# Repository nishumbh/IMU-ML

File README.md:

# Knee rehabilitation: IMU-only offline model training

Research pipeline for knee rehabilitation form assessment using KneE-PAD IMU
data: verified release ingestion, preprocessing, subject-disjoint evaluation,
and saved scikit-learn models. **Current scope is offline training and model
storage, not embedded deployment.** This is not a clinical model or a
safety-certified device.

The local `data/raw/dataset` release has 2,086 trials from 31 participants. Its
48-channel layout, 148.14814814814815 Hz rate, units and nine source class IDs
were checked against the [release metadata](https://zenodo.org/records/12112951)
and [paper](https://doi.org/10.1038/s41597-025-04963-4). Separate squat, seated
leg-extension and gait manifests preserve the two documented errors per task.
Two gait files are empty and require explicit, recorded exclusion.

**Important limits:** the reference models use all eight IMUs (48 channels),
not a single-IMU knee brace. Use `--sensor-ids` to define a fixed subset and
retrain/evaluate it separately. No injured-side swapping, mirroring or frame
alignment is inferred. Generic manifest templates still need verified mappings
for other releases. Supplementary pretraining/domain adaptation is not
implemented. TensorFlow remains optional; embedded functionality is deferred.

## Two-strap ESP32-C3 prototype

For the **two-board MicroPython + ESP-NOW + master SD** implementation, see
[`tech/iot/README.md`](tech/iot/README.md). It has hardcoded bench and provisioned
OTA-capable iterations. Mechanical/electronics assets remain in `tech/designs/`.
The older Arduino sketch below is a separate, single-board acquisition example.

For the above-knee / below-knee two-IMU hardware, start with
[docs/TWO_STRAP_TEAM_GUIDE.md](docs/TWO_STRAP_TEAM_GUIDE.md). It covers wiring,
SD logging, sensor placement, CSV format and the local browser interface.

```bash
# Run from project root; review-only, no hardware/model required:
PYTHONPATH=src python -m knee_rehab.interface
# Enable offline research predictions using a separately trained 12-channel model:
PYTHONPATH=src python -m knee_rehab.interface \
  --model-dir artifacts/knee_pad_extension_two_imu_rf_v1
```

Open `http://127.0.0.1:8080` and upload the SD recording. The example Arduino
logger is `firmware/two_imu_logger/two_imu_logger.ino` (two **MPU6050** modules;
change drivers for other IMUs). This is SD-to-computer review, not live medical
feedback or on-ESP32 inference. Firmware hardware testing remains outstanding.
The two-sensor models were genuinely retrained on thigh/shank source sensors,
not padded to imitate eight sensors. Their performance is limited; see the
team guide before interpreting any prediction.

## Directory layout

```text
.
├── README.md
├── pyproject.toml
├── requirements.txt
├── configs/
│   ├── manifest.example.json               # Numeric KneE-PAD NPY mapping template
│   ├── manifest.csv.example.json           # Supplementary CSV mapping template
│   └── resource_measurements.example.json  # Null/unverified: intentionally fails gate
├── src/knee_rehab/
│   ├── __init__.py
│   ├── data_loader.py                      # Explicit, SI-unit IMU-only NPY/CSV ingestion
│   ├── preprocess.py                       # Resampling, causal DSP, windows, cheap features
│   ├── baseline.py                         # Bounded RF and scaled RBF SVM; LOSO
│   ├── models.py                           # Compact temporal CNN; fold-local channel scaling
│   ├── evaluate.py                         # Fixed confusion matrices + false acceptance
│   ├── export.py                           # Training-calibrated full-int8 TFLite export
│   ├── check_resources.py                  # Fail-closed measured-resource gate
│   └── train.py                            # CLI + artifacts/provenance
├── scripts/create_demo_data.py             # SYNTHETIC mixed-format smoke test only
├── tests/
│   ├── test_data_loader.py
│   ├── test_preprocess.py
│   ├── test_evaluation.py
│   ├── test_resources.py
│   └── test_export.py                      # Skipped without TensorFlow
├── docs/DATASETS.md                        # Mapping, alignment, labels, integration rules
├── firmware/README.md                      # MCU numerical parity and memory acceptance
├── data/
│   ├── raw/                               # External, untracked, immutable sources
│   ├── interim/                           # Verified conversions/alignment
│   └── processed/                         # Optional cached windows/features
├── artifacts/                             # One new/empty directory per training run
└── notebooks/                             # Optional exploratory analysis
```

## Install and run

Python 3.10–3.13; Python 3.11/3.12 is a practical choice for TensorFlow wheel
availability on supported platforms.

```bash
python -m venv .venv
source .venv/bin/activate
python -m pip install -r requirements.txt
python -m pip install -e .

# No dataset credentials required: SYNTHETIC pipeline smoke test only
python scripts/create_demo_data.py
python -m knee_rehab.train \
  --manifest data/demo_manifest.json --output-dir artifacts/demo_rf \
  --model rf --correct-threshold 0.9

python -m knee_rehab.train \
  --manifest data/demo_manifest.json --output-dir artifacts/demo_svm \
  --model svm --correct-threshold 0.9

# Tests work with the standard library, without pytest
PYTHONPATH=src python -m unittest discover -s tests -v
# Or: pip install -e '.[dev]' && pytest
```

Synthetic results test plumbing, **not** rehabilitation accuracy. The demo has
four fake participants and three deliberately separable simulated classes. Use
a distinct empty output directory for every run to prevent stale model/report
mixups. Recent scikit-learn versions may warn that SVC's probability API is
being deprecated; this baseline currently uses that API.

For real data, copy a manifest template, replace all placeholders from the
actual release and follow [docs/DATASETS.md](docs/DATASETS.md). Then:

```bash
python -m knee_rehab.train \
  --manifest configs/my_verified_knee_pad.json \
  --output-dir artifacts/knee_pad_rf_v1 --model rf \
  --target-rate-hz 50 --cutoff-hz 10 --filter-order 4 \
  --window-seconds 2 --overlap 0.5 --correct-threshold 0.9
```

`0.9` is an **illustrative prespecified threshold**, not a validated safety
setting. Estimate a clinically acceptable operating point using inner,
subject-disjoint validation and a separate outer/prospective evaluation. Do not
tune a threshold on the held-out participant.

## Train and store models from the local release

The completed reference run and saved artifact paths are documented in
[docs/TRAINING_RESULTS.md](docs/TRAINING_RESULTS.md), including the low recall
at the illustrative 0.9 threshold and the source exclusions.

Run from the project root. No TensorFlow, firmware, quantization, or target
hardware is required for the random forest models. Pick new manifest/output
paths if these already exist; the commands intentionally refuse overwrites.

```bash
# Build exercise-specific manifests; checks shapes, units and source SHA-256.
for exercise in extension squat gait; do
  python -m knee_rehab.knee_pad \
    --dataset-dir data/raw/dataset --exercise "$exercise" --skip-empty \
    --output "data/interim/knee_pad_${exercise}_all_imus.json"
done

# LOSO evaluation, followed by a final fit on all available subjects.
for exercise in extension squat gait; do
  python -m knee_rehab.train \
    --manifest "data/interim/knee_pad_${exercise}_all_imus.json" \
    --output-dir "artifacts/knee_pad_${exercise}_rf_v1" \
    --model rf --correct-threshold 0.9
done
```

`--skip-empty` only permits explicit exclusion of fewer-than-two-sample trials;
NaN/Inf, unknown class folders and invalid channel layouts still fail. Excluded
paths, shapes, reasons and hashes are retained in the manifest. The two empty
files are `Subject_18/6/Trial_1/imu.npy` and `Subject_27/6/Trial_1/imu.npy`.
Raw files are never modified. All eight fixed anatomical sensor placements are
used by default. For a single fixed right rectus femoris IMU, build a **new**
manifest with `--sensor-ids 1`; this is not automatically the injured leg.

Each output directory stores:

- `final.joblib`: final RF pipeline, fitted on all included subjects;
- `cv_results.json`: held-out-subject and pooled raw/conservative results;
- `metadata.json`: ordered channels, labels, preprocessing, window/subject
  counts, skipped recordings, source hashes and Python/package versions;
- `feature_config.json`, `feature_names.json`: exact feature mapping;
- `input_manifest.json`: original mapping/provenance snapshot. Its relative
  paths are anchored to the original `manifest_path` in metadata, not to the
  snapshot's new directory; use the original manifest for replay.

`artifacts/` and `data/interim/` are gitignored: keep a separate backup of model
artifacts and manifests. Joblib files must only be loaded from trusted sources,
using compatible package versions (recorded in metadata).

### Reload for offline predictions

```bash
python -m knee_rehab.predict \
  --model-dir artifacts/knee_pad_extension_rf_v1 \
  --manifest data/interim/knee_pad_extension_all_imus.json \
  --output artifacts/extension_predictions.json
```

This reuses saved preprocessing and checks channel compatibility. Predictions
on the training manifest are a persistence/plumbing check, **not** a new test
score; use `cv_results.json` for LOSO results. The exercise must already be known:
these are three form models, not an automatic exercise recognizer. Gait has far
fewer trials and missing class coverage per subject. A 0.9 rejection threshold
is illustrative, not clinically validated; low false acceptance alone does not
mean useful correct-form recall.

## Data loading and preprocessing APIs

```python
from knee_rehab.data_loader import load_manifest
from knee_rehab.preprocess import PreprocessConfig, prepare_windows, extract_features

recordings = load_manifest("configs/my_verified_knee_pad.json")
batch = prepare_windows(recordings, PreprocessConfig(
    target_rate_hz=50, cutoff_hz=10, filter_order=4,
    window_seconds=2, overlap=0.5,
))
features, names = extract_features(batch.X, batch.sample_rate_hz)
# batch.X: float32 [windows, 100 samples, channels]
# batch.y / batch.subject_ids / batch.recording_ids: one value per window
# Six IMU channels -> features.shape == (windows, 84)
```

Each manifest record is one contiguous, constant-label, single-subject trial
segment. Paths are relative to the manifest. Only selected acceleration and
rotation channels are read into model inputs; sEMG, pressure, magnetometer,
subject information and labels never become features. Subject information is
retained only for grouping/evaluation. Acceleration/rotation are converted to
m/s² and rad/s. Missing/invalid readings and irregular timestamps are rejected
rather than silently dropping rows or mixing samples across gaps.

Processing order per record:

1. `resample_poly`: rational polyphase conversion, including anti-aliasing for
   downsampling. This is an **offline, noncausal** FIR. It is not the MCU's causal
   Butterworth filter. Acquire directly at the target rate on-device, or validate
   a streaming rate converter with the same effective transfer function/delay.
2. Butterworth low-pass using **causal** second-order sections (`sosfilt`), not
   `filtfilt`. Initialize using `sosfilt_zi * first_channel_value`. Retain state
   across windows; reset only at stream/segment boundaries. Audit startup effects
   and transition latency before deploying.
3. Full, unpadded fixed windows. Default: 100 samples and 50-sample hop at 50 Hz.
   Hop is `round(window_samples * (1-overlap))`, so arbitrary requested overlap is
   sample-rounded. Trailing partial windows are discarded; too-short records are
   reported and skipped. Windows never cross label, subject or recording bounds.

Fixed windows are **not automatically discrete repetitions**. Repetition onset,
exercise recognition, a resting/unknown state and temporal decision smoothing
require separately validated logic. No augmentation or learned preprocessing
runs before LOSO splitting.

### Features that can be ported to C/C++

Per channel, in this order:

- Mean, population variance, standard deviation, population skewness, demeaned
  zero-crossing rate, minimum, maximum, RMS and peak-to-peak amplitude.
- Demeaned rectangular-window Goertzel power at 0.5, 1, 2, 3 and 5 Hz, normalized
  by `N*N`. These are **frequency probes**, not broadband energy or a full FFT.

14 features/channel, channel-major. Mean/variance/skewness use finite sums;
constants produce zero skewness and zero ZCR. A standard-deviation floor of
`1e-8` stabilizes skewness. ZCR treats exactly zero as nonnegative and divides by
`N-1`. Goertzel uses precomputed `2*cos(2*pi*f/fs)` coefficients and only basic
addition/multiplication per sample. Square root is needed for std/RMS. There is
no runtime SciPy/stats/FFT dependency in the algorithm that must be ported.
Change the function's probe frequencies for low-rate applications; the CLI's
default probes require a target rate strictly above 10 Hz.

## Training and evaluation

- **RF:** 64 trees, depth capped at 6, minimum leaf size 2, balanced class weights.
  A baseline for comparison, not automatically an MCU-compatible executable.
- **SVM:** RBF SVC with `StandardScaler` inside each fold's pipeline and balanced
  class weights. Support-vector size can grow; no ESP32 size promise. Internal
  SVC probability calibration uses training-fold data, not the held-out subject;
  it is not a substitute for subject-grouped clinical threshold validation.
- **CNN:** two temporal convolution blocks (8 and 12 filters), two max pools,
  flatten and softmax dense output. Expressed as `(k,1)` Conv2D for TFLM-friendly
  operator support. No LSTM, batch norm, dropout or embedded floating normalizer.
  Per-channel means/scales are fitted on training folds only. Fixed epochs avoid
  selecting epochs using the outer held-out participant.

LOSO holds out **all windows/sessions of each actual person**. Dataset-specific
participant IDs must be globally unambiguous. Each fold must have at least two
training classes; missing other classes are reported, with a fixed label order
and zero-support-safe metrics. Class names are manifest driven: preserve
`Incomplete Extension` separately from `Incomplete Flexion` when appropriate.
Unassessed or pretraining-only supplementary records are rejected by the
supervised training CLI.

`cv_results.json` contains per-subject and pooled confusion matrices (rows=true,
columns=predicted), per-class precision/recall/F1 and safety metrics:

```text
false acceptance rate = actual incorrect windows predicted Correct Form
                       / all actual incorrect windows
```

If there are no incorrect examples the rate is `null`, not a misleading zero.
With `--correct-threshold`, a winning correct-class prediction below the
threshold becomes `__REJECT__`; no other class is promoted to Correct Form.
Both raw and conservative reports are retained. Unknown real-world movements
can still be falsely accepted: confidence thresholding is **not OOD detection**.

Never randomly split overlapping windows into train/test. Windows from one
participant are correlated: a large window count is not a large independent
sample size. Per-subject results should drive failure analysis. Comparing many
models/thresholds on the same LOSO folds and reporting the winner's LOSO score
as unbiased is invalid; add nested grouped selection or an independent
prospective cohort. For multiple exercise types, also stratify errors by exercise
and prevent exercise/dataset identity from becoming a proxy for form.

After CV, the CLI fits a final model on **all supplied participants** for storage.
That fit is explicitly marked non-evaluation. Artifacts include the manifest
snapshot/hash, class/channel mapping, preprocessing coefficients and metadata,
CV results and `final.joblib` or `final.keras`. Do not load joblib artifacts from
untrusted sources. Source data checksums/environment lockfiles should be added
for a regulated/reproducible study.

## Optional CNN and int8 edge export

```bash
pip install -e '.[train]'
python -m knee_rehab.train \
  --manifest configs/my_verified_knee_pad.json \
  --output-dir artifacts/knee_pad_cnn_v1 --model cnn \
  --epochs 15 --batch-size 32 --correct-threshold 0.9 \
  --export-int8 --max-flash-bytes 262144 --calibration-windows 256
```

Without `--export-int8`, CNN training only stores the Keras model, scaling,
metadata and CV results. The explicit optional flag above additionally enables
legacy edge export; it is outside the current offline-only scope. With the
flag, training writes:

- `final.keras`, `scaling.json`, `metadata.json`, `cv_results.json`;
- `final.int8.tflite` with **int8 input/output** and integer-only converter ops;
- `final.int8.tflite.deployment.json`, including model bytes/hash,
  quantization parameters, operators and explicit unverified deployment status.

The 256 KiB model-only flash cap is an **example reservation**, not the usable
flash of every ESP32. Override it using your partition and firmware budgets.
Exceeding it fails export without writing the new `.tflite` file. Representative
samples are drawn only from the model's training data. In the final all-input
fit, all supplied subjects are training subjects; the export has no remaining
independent validation set. To quantize inside LOSO, call `export_int8` with only
that fold's training windows and assess the resulting artifact on that fold's
held-out subject. That quantized LOSO loop is not implemented here.

Current CV reports describe **float CNN predictions**, not int8 performance.
Quantized accuracy, especially false acceptance, must be tested before use.
Conversion and CNN runtime were not exercised in the initial environment
because TensorFlow was absent; `tests/test_export.py` runs conversion when the
extra is installed. See [firmware/README.md](firmware/README.md) for the strict
resource gate and required target measurements.

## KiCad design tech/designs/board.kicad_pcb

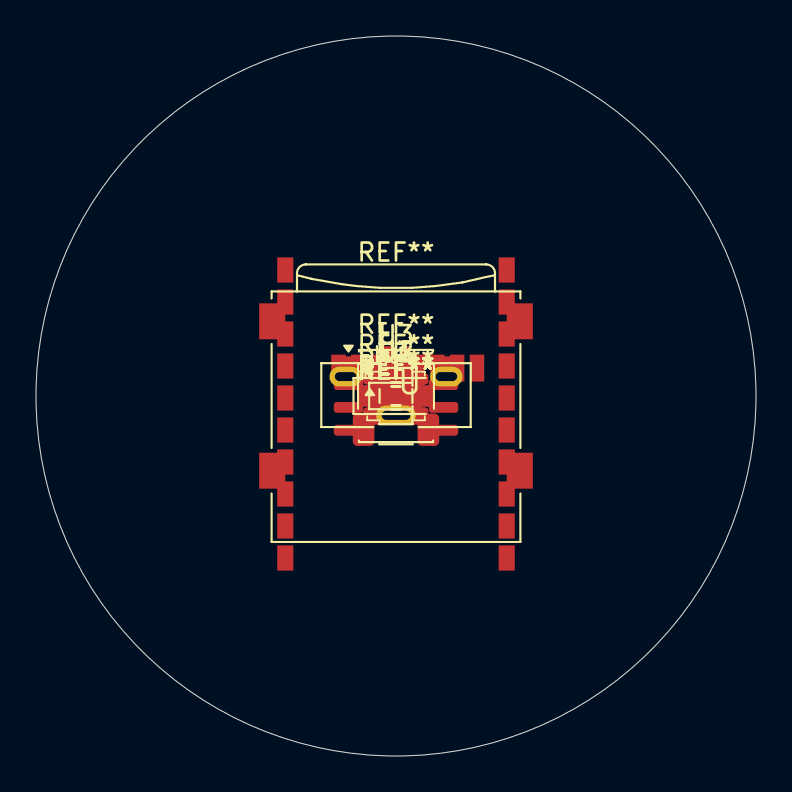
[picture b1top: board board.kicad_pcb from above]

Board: 2 copper layers, 40.0 x 40.0 mm, 5 parts (0 on the bottom side), 5 nets, no tracks yet.

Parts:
Q1: AO3401A; SOT-23-3
U: ESP32_C3_MINI_1
U2: LSM6DSO; Bosch_LGA-14_3x2.5mm_P0.5mm
U3: TP4056; SOIC-8-1EP_3.9x4.9mm_P1.27mm_EP2.514x3.2mm
U4: HT7833; SOT-23-5

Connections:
3V3: U2.4 (CS), U2.7 (VDD), U2.9 (VDDIO), U4.1 (VOUT)
BAT: Q1.3 (Drain), U3.3 (BAT)
GND: U2.1 (SDO/SA0), U2.8 (GND), U3.6 (GND), U4.2 (GND)
VBUS: Q1.1 (Gate), U3.2 (VCC)
VSYS: Q1.2 (Source), U4.3 (VIN), U4.4 (EN)
